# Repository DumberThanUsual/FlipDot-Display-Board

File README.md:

# flipdot Display Board
Internet connected display built with magnetically flipped coloured discs

Final design and software incomplete - repo will be reorganised when finished

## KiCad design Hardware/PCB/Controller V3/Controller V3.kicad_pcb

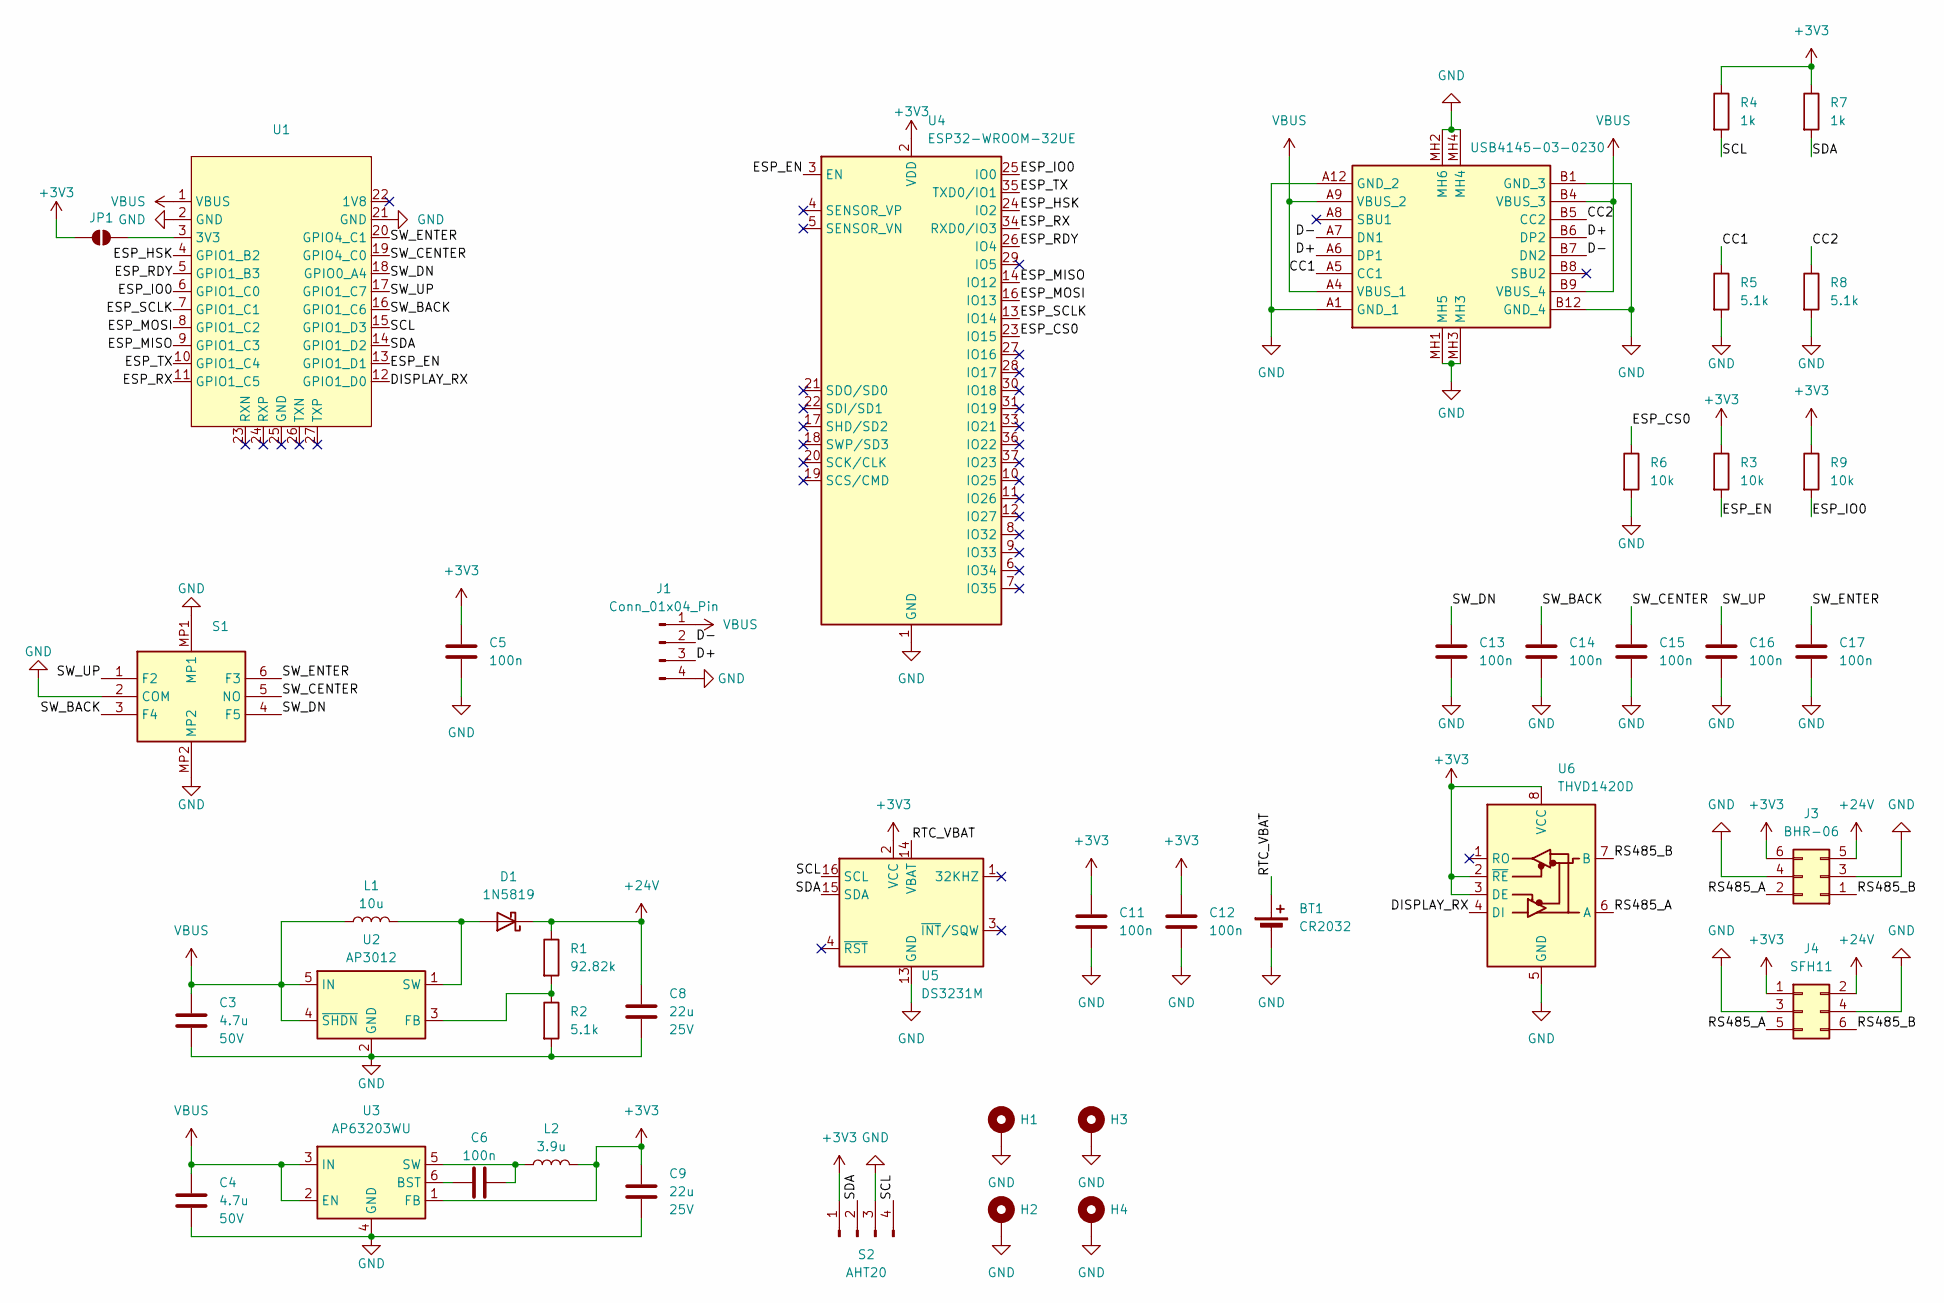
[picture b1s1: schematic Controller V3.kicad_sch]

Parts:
BT1: CR2032; S8411-45
C3, C4: 4.7u; C_0805_2012Metric; Voltage 50V
C5, C6, C11, C12, C13, C14, C15, C16, C17: 100n; C_0603_1608Metric
C8, C9: 22u; C_0805_2012Metric; Voltage 25V
D1: 1N5819; Nexperia_CFP3_SOD-123W
H1, H2, H3, H4: MountingHole_Pad; MountingHole_3.2mm_M3_DIN965_Pad
J1: Conn_01x04_Pin; PinHeader_1x04_P2.54mm_Vertical
J2: USB4145-03-0230; USB4145030230C; Mouser Part Number 640-USB4145-3-0230-C
J3: BHR-06; PinHeader_2x03_P2.54mm_Horizontal
J4: SFH11; PinSocket_2x03_P2.54mm_Vertical
JP1: SolderJumper_2_Open; SolderJumper-2_P1.3mm_Open_RoundedPad1.0x1.5mm
L1: 10u; L_Bourns-SRN6028
L2: 3.9u; L_Bourns-SRN6028
R1: 92.82k; R_0603_1608Metric
R2, R5, R8: 5.1k; R_0603_1608Metric
R3, R6, R9: 10k; R_0603_1608Metric
R4, R7: 1k; R_0603_1608Metric
S1: TS12-74-70-BK-250-SMT-TR; TS127460BK250SMTTR; Mouser Part Number 179-TS127460250SMTTR
S2: AHT20; PinHeader_1x04_P2.54mm_Vertical
U1: Pico Mini
U2: AP3012; SOT-23-5
U3: AP63203WU; TSOT-23-6
U4: ESP32-WROOM-32UE
U5: DS3231M; SOIC-16W_7.5x10.3mm_P1.27mm
U6: THVD1420D; SOIC-8_3.9x4.9mm_P1.27mm

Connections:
+3V3: C5.1, C9.1, C11.1, C12.1, J3.6, J4.1, JP1.1 (A), L2.2, R3.1, R4.1, R7.1, R9.1, S2.1, U3.1 (FB), U4.2 (VDD), U5.2 (VCC), U6.2 (~RE), U6.3 (DE), U6.8 (VCC)
+24V: C8.1, D1.1 (K), J3.5, J4.2, R1.1
/CC1: J2.A5 (CC1), R5.1
/CC2: J2.B5 (CC2), R8.1
/D+: J1.3, J2.A6 (DP1), J2.B6 (DP2)
/D-: J1.2, J2.A7 (DN1), J2.B7 (DN2)
/DISPLAY_RX: U1.12 (GPIO1_D0), U6.4 (DI)
/ESP_CS0: R6.1, U4.23 (IO15)
/ESP_EN: R3.2, U1.13 (GPIO1_D1), U4.3 (EN)
/ESP_HSK: U1.4 (GPIO1_B2), U4.24 (IO2)
/ESP_IO0: R9.2, U1.6 (GPIO1_C0), U4.25 (IO0)
/ESP_MISO: U1.9 (GPIO1_C3), U4.14 (IO12)
/ESP_MOSI: U1.8 (GPIO1_C2), U4.16 (IO13)
/ESP_RDY: U1.5 (GPIO1_B3), U4.26 (IO4)
/ESP_RX: U1.11 (GPIO1_C5), U4.34 (RXD0/IO3)
/ESP_SCLK: U1.7 (GPIO1_C1), U4.13 (IO14)
/ESP_TX: U1.10 (GPIO1_C4), U4.35 (TXD0/IO1)
/RS485_A: J3.2, J4.5, U6.6 (A)
/RS485_B: J3.1, J4.6, U6.7 (B)
/RTC_VBAT: BT1.1 (+), U5.14 (VBAT)
/SCL: R4.2, S2.4, U1.15 (GPIO1_D3), U5.16 (SCL)
/SDA: R7.2, S2.2, U1.14 (GPIO1_D2), U5.15 (SDA)
/SW_BACK: C14.1, S1.3 (F4), U1.16 (GPIO1_C6)
/SW_CENTER: C15.1, S1.5 (NO), U1.19 (GPIO4_C0)
/SW_DN: C13.1, S1.4 (F5), U1.18 (GPIO0_A4)
/SW_ENTER: C17.1, S1.6 (F3), U1.20 (GPIO4_C1)
/SW_UP: C16.1, S1.1 (F2), U1.17 (GPIO1_C7)
GND: BT1.2 (-), C3.2, C4.2, C5.2, C8.2, C9.2, C11.2, C12.2, C13.2, C14.2, C15.2, C16.2, C17.2, H1.1, H2.1, H3.1, H4.1, J1.4, J2.A1 (GND_1), J2.A12 (GND_2), J2.B1 (GND_3), J2.B12 (GND_4), J2.MH1 (MH5), J2.MH2 (MH6), J2.MH3, J2.MH4, J3.3, J3.4, J4.3, J4.4, R2.2, R5.2, R6.2, R8.2, S1.2 (COM), S1.MP1, S1.MP2, S2.3, U1.2 (GND), U1.21 (GND), U2.2 (GND), U3.4 (GND), U4.1 (GND), U4.15 (GND), U4.38 (GND), U4.39 (GND), U5.5 (GND), U5.6 (GND), U5.7 (GND), U5.8 (GND), U5.9 (GND), U5.10 (GND), U5.11 (GND), U5.12 (GND), U5.13 (GND), U6.5 (GND)
unnamed: D1.2 (A), L1.2, U2.1 (SW)
unnamed: JP1.2 (B), U1.3 (3V3)
unnamed: R1.2, R2.1, U2.3 (FB)
unnamed: C6.1, U3.6 (BST)
unnamed: C6.2, L2.1, U3.5 (SW)
VBUS: C3.1, C4.1, J1.1, J2.A4 (VBUS_1), J2.A9 (VBUS_2), J2.B4 (VBUS_3), J2.B9 (VBUS_4), L1.1, U1.1 (VBUS), U2.4 (~SHDN), U2.5 (IN), U3.2 (EN), U3.3 (IN)

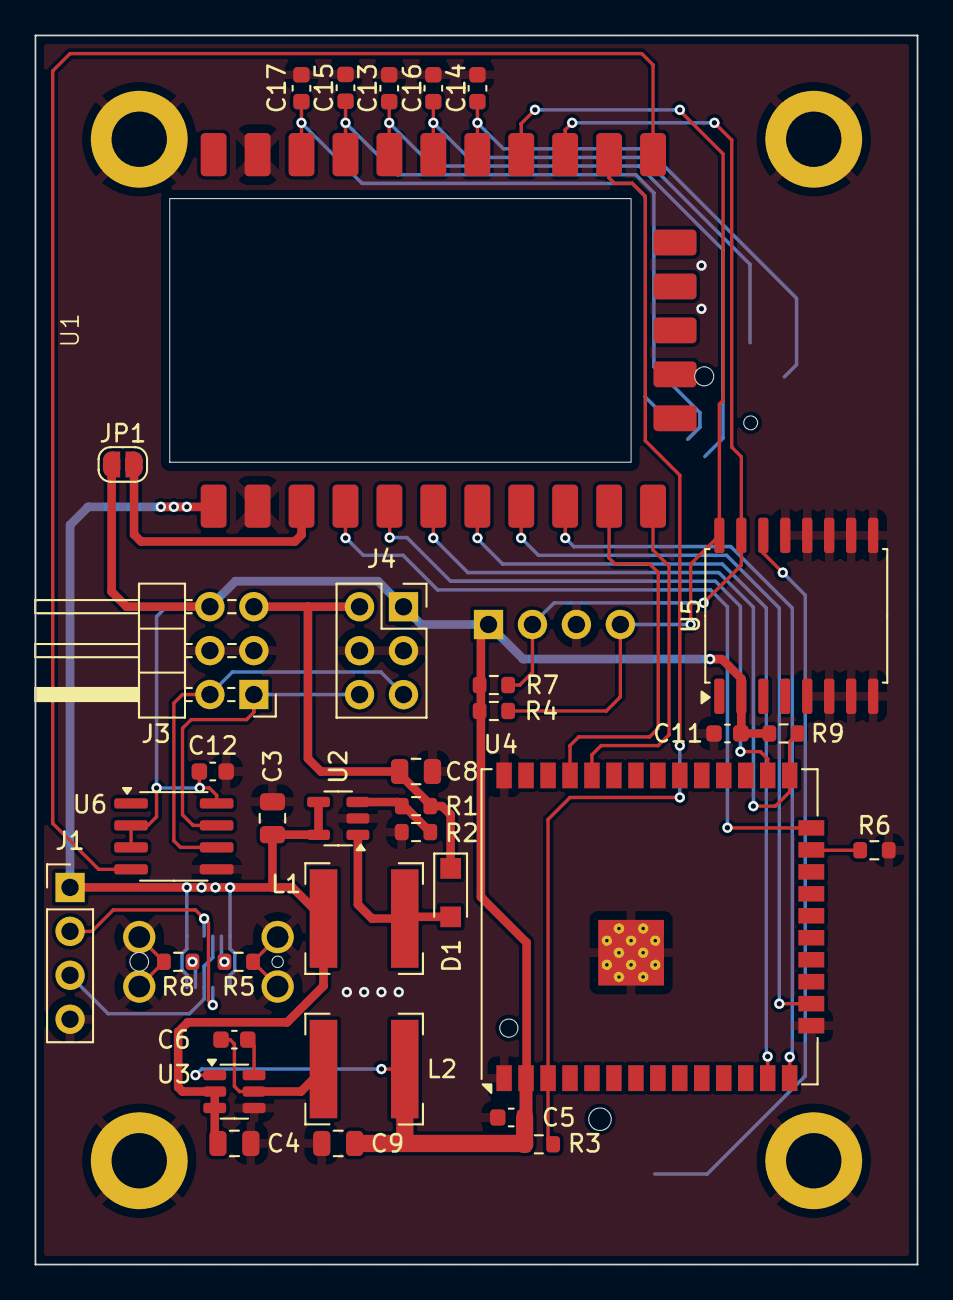
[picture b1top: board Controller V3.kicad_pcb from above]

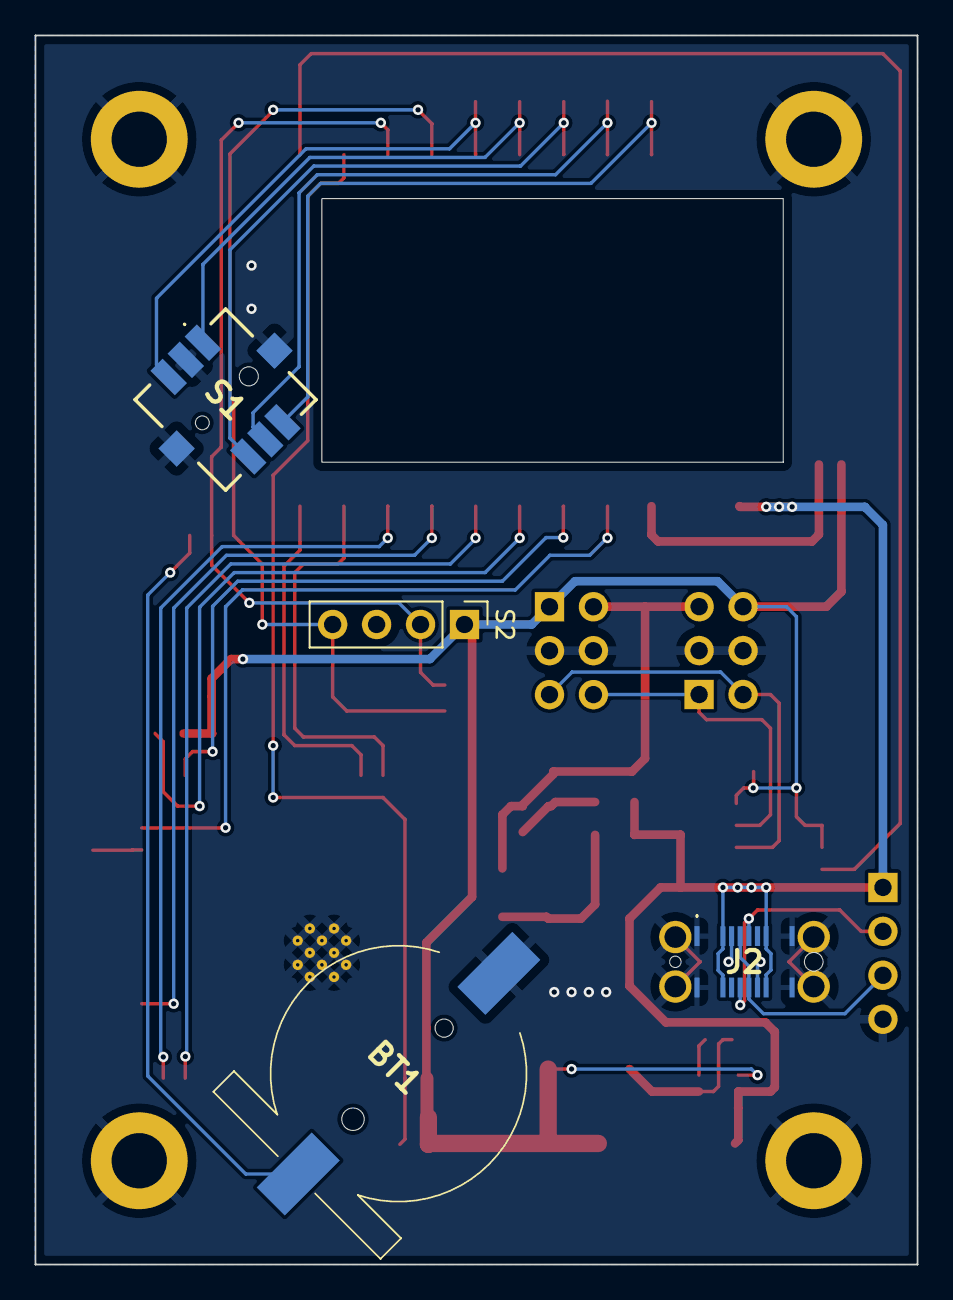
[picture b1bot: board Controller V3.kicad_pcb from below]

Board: 2 copper layers, 51.0 x 71.0 mm, 43 parts (4 on the bottom side), 34 nets.

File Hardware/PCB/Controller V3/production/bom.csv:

Designator,Footprint,Quantity,Value,LCSC Part #
BT1,S8411-45,1,CR2032,
"C11, C12, C13, C14, C15, C16, C17, C5, C6",0603,9,100n,
"C3, C4",0805,2,4.7u,
"C8, C9",0805,2,22u,
D1,Nexperia_CFP3_SOD-123W,1,1N5819,
"H1, H2, H3, H4",MountingHole_3.2mm_M3_DIN965_Pad,4,MountingHole_Pad,
J1,PinHeader_1x04_P2.54mm_Vertical,1,Conn_01x04_Pin,
J2,USB4145030230C,1,USB4145-03-0230,
J3,PinHeader_2x03_P2.54mm_Horizontal,1,BHR-06,
J4,PinSocket_2x03_P2.54mm_Vertical,1,SFH11,
L1,L_Bourns-SRN6028,1,10u,
L2,L_Bourns-SRN6028,1,3.9u,
R1,0603,1,92.82k,
"R2, R5, R8",0603,3,5.1k,
"R3, R6, R9",0603,3,10k,
"R4, R7",0603,2,1k,
S1,TS127460BK250SMTTR,1,TS12-74-70-BK-250-SMT-TR,
S2,PinHeader_1x04_P2.54mm_Vertical,1,AHT20,
U1,Pico Mini,1,~,
U2,SOT-23-5,1,AP3012,
U3,TSOT-23-6,1,AP63203WU,
U4,ESP32-WROOM-32UE,1,ESP32-WROOM-32UE,
U5,SOIC-16W_7.5x10.3mm_P1.27mm,1,DS3231M,
U6,SOIC-8_3.9x4.9mm_P1.27mm,1,THVD1420D,
